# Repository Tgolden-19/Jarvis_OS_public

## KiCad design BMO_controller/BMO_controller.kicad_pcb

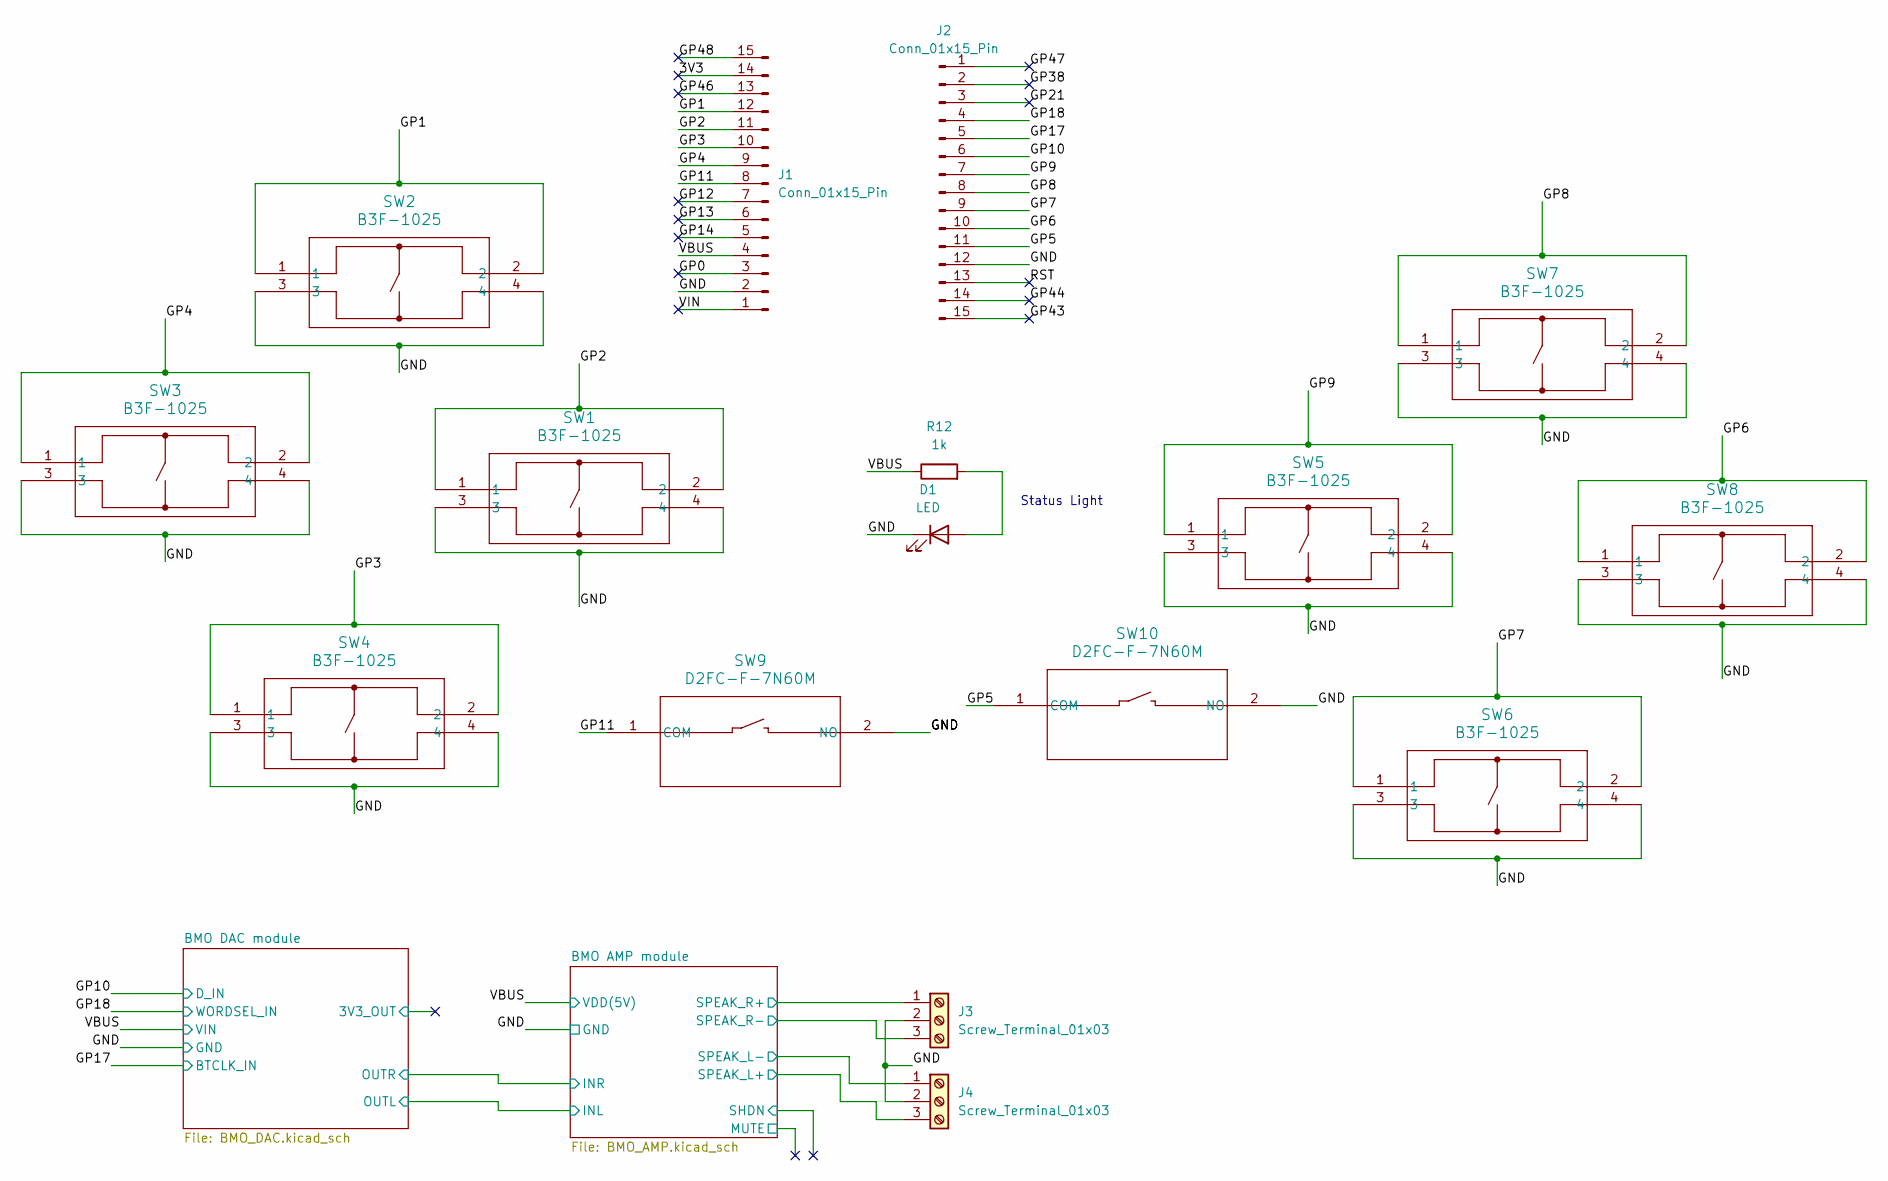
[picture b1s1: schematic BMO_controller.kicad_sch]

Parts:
D1: LED; LED_0201_0603Metric
J1, J2: Conn_01x15_Pin; PinSocket_1x15_P2.54mm_Vertical
J3, J4: Screw_Terminal_01x03; TerminalBlock_4Ucon_1x03_P3.50mm_Horizontal
R12: 1k; R_0201_0603Metric
SW1, SW2, SW3, SW4, SW5, SW6, SW7, SW8: B3F-1025; SW_B3F-1000_OMR
SW9, SW10: D2FC-F-7N60M; SW_D2FC_OMR

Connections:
/3V3: J1.14
/BMO AMP module/SPEAK_L+: J4.3; also elsewhere on the board
/BMO AMP module/SPEAK_L-: J4.1; also elsewhere on the board
/BMO AMP module/SPEAK_R+: J3.1; also elsewhere on the board
/BMO AMP module/SPEAK_R-: J3.3; also elsewhere on the board
/GP0: J1.3
/GP1: J1.12, SW2.1, SW2.2
/GP2: J1.11, SW1.1, SW1.2
/GP3: J1.10, SW4.1, SW4.2
/GP4: J1.9, SW3.1, SW3.2
/GP5: J2.11, SW10.1 (COM)
/GP6: J2.10, SW8.1, SW8.2
/GP7: J2.9, SW6.1, SW6.2
/GP8: J2.8, SW7.1, SW7.2
/GP9: J2.7, SW5.1, SW5.2
/GP10: J2.6; also elsewhere on the board
/GP11: J1.8, SW9.1 (COM)
/GP12: J1.7
/GP13: J1.6
/GP14: J1.5
/GP17: J2.5; also elsewhere on the board
/GP18: J2.4; also elsewhere on the board
/GP21: J2.3
/GP38: J2.2
/GP43: J2.15
/GP44: J2.14
/GP46: J1.13
/GP47: J2.1
/GP48: J1.15
/RST: J2.13
/VBUS: J1.4, R12.1; also elsewhere on the board
/VIN: J1.1
GND: D1.1 (K), J1.2, J2.12, J3.2, J4.2, SW1.3, SW1.4, SW2.3, SW2.4, SW3.3, SW3.4, SW4.3, SW4.4, SW5.3, SW5.4, SW6.3, SW6.4, SW7.3, SW7.4, SW8.3, SW8.4, SW9.2 (NO), SW10.2 (NO); also elsewhere on the board
unnamed: D1.2 (A), R12.2

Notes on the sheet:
Status Light

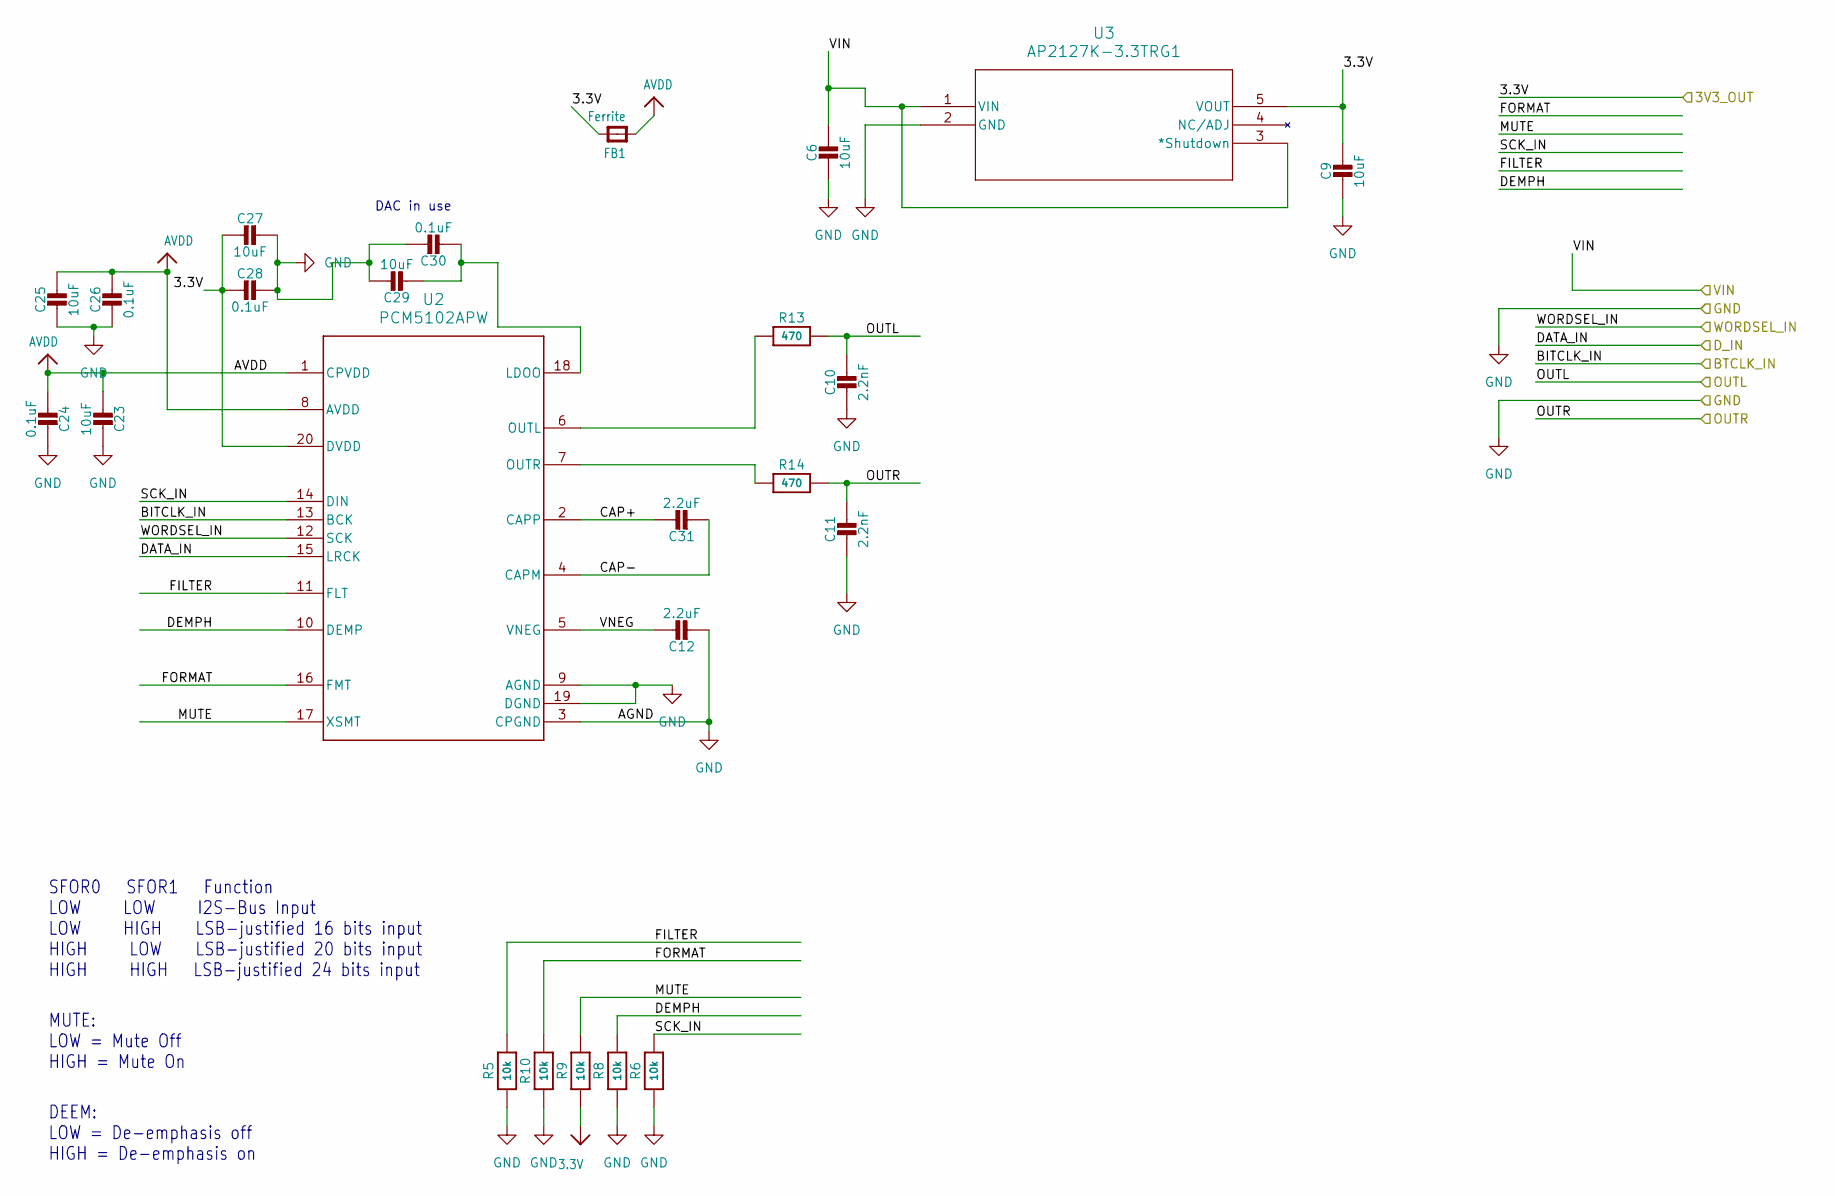
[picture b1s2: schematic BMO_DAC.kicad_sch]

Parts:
C6, C9, C23, C25, C27, C29: 10uF; C_0805_2012Metric
C10, C11: 2.2nF; C_0603_1608Metric
C12, C31: 2.2uF; C_0603_1608Metric
C24, C26, C28, C30: 0.1uF; C_0603_1608Metric
FB1: Ferrite; R_0603_1608Metric_Pad0.98x0.95mm_HandSolder
R5, R6, R8, R9, R10: 10k; R_0603_1608Metric
R13, R14: 470; R_0402_1005Metric
U2: PCM5102APW; PW0020A_M
U3: AP2127K-3.3TRG1; SOT-23-5_AP2127K-3.3TRG1_DIO

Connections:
3.3V: C9.1, C27.1, C28.1, FB1.2, R9.1, U2.20 (DVDD), U3.5 (VOUT)
/BMO DAC module/CAP+: C31.1, U2.2 (CAPP)
/BMO DAC module/CAP-: C31.2, U2.4 (CAPM)
/BMO DAC module/DEMPH: R8.2, U2.10 (DEMP)
/BMO DAC module/FILTER: R5.2, U2.11 (FLT)
/BMO DAC module/FORMAT: R10.2, U2.16 (FMT)
/BMO DAC module/MUTE: R9.2, U2.17 (XSMT)
/BMO DAC module/OUTL: C10.1, R13.2; also elsewhere on the board
/BMO DAC module/OUTR: C11.1, R14.2; also elsewhere on the board
/BMO DAC module/SCK_IN: R6.2, U2.14 (DIN)
/BMO DAC module/VNEG: C12.1, U2.5 (VNEG)
/GP10: U2.15 (LRCK); also elsewhere on the board
/GP17: U2.13 (BCK); also elsewhere on the board
/GP18: U2.12 (SCK); also elsewhere on the board
/VBUS: C6.1, U3.1 (VIN), U3.3 (*Shutdown); also elsewhere on the board
AVDD: C23.1, C24.1, C25.1, C26.1, FB1.1, U2.1 (CPVDD), U2.8 (AVDD)
GND: C6.2, C9.2, C10.2, C11.2, C12.2, C23.2, C24.2, C25.2, C26.2, C27.2, C28.2, C29.2, C30.2, R5.1, R6.1, R8.1, R10.1, U2.3 (CPGND), U2.9 (AGND), U2.19 (DGND), U3.2 (GND); also elsewhere on the board
unnamed: C29.1, C30.1, U2.18 (LDOO)
unnamed: R13.1, U2.6 (OUTL)
unnamed: R14.1, U2.7 (OUTR)

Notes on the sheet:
MUTE: LOW = Mute Off HIGH = Mute On
SFOR0 SFOR1 Function LOW LOW I2S-Bus Input LOW HIGH LSB-justified 16 bits input HIGH LOW LSB-justified 20 bits input HIGH HIGH LSB-justified 24 bits input
DAC in use
DEEM: LOW = De-emphasis off HIGH = De-emphasis on

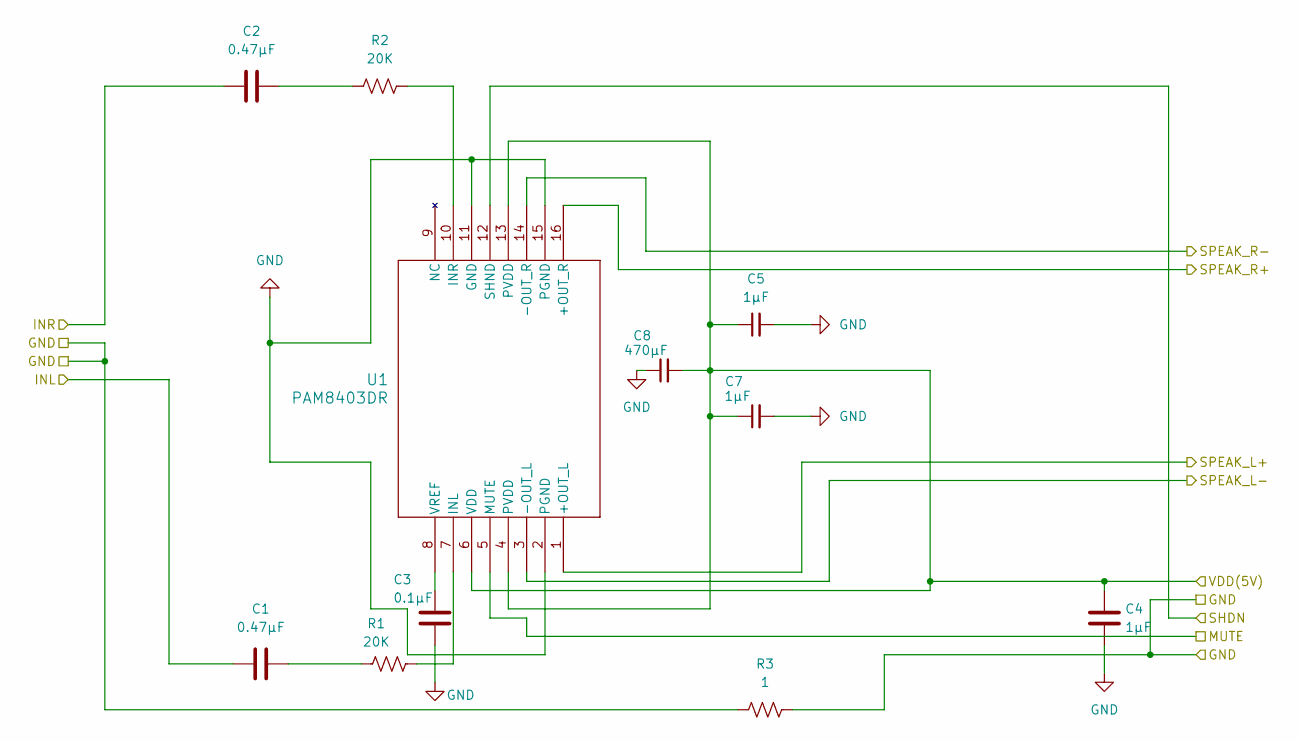
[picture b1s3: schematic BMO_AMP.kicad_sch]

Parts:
C1, C2: 0.47µF; C_0603_1608Metric
C3: 0.1µF; C_0603_1608Metric
C4, C5, C7: 1µF; C_0603_1608Metric
C8: 470µF; C_1812_4532Metric
R1, R2: 20K; R_0603_1608Metric
R3: 1; R_0201_0603Metric
U1: PAM8403DR; SOIC_8403DR_DIO

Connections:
/BMO AMP module/MUTE: U1.5 (MUTE)
/BMO AMP module/SHDN: U1.12 (SHND)
/BMO AMP module/SPEAK_L+: U1.1 (+OUT_L); also elsewhere on the board
/BMO AMP module/SPEAK_L-: U1.3 (-OUT_L); also elsewhere on the board
/BMO AMP module/SPEAK_R+: U1.16 (+OUT_R); also elsewhere on the board
/BMO AMP module/SPEAK_R-: U1.14 (-OUT_R); also elsewhere on the board
/BMO DAC module/OUTL: C1.1; also elsewhere on the board
/BMO DAC module/OUTR: C2.1; also elsewhere on the board
/VBUS: C4.2, C5.1, C7.1, C8.2, U1.4 (PVDD), U1.6 (VDD), U1.13 (PVDD); also elsewhere on the board
GND: C3.1, C4.1, C5.2, C7.2, C8.1, R3.1, R3.2, U1.2 (PGND), U1.11 (GND), U1.15 (PGND); also elsewhere on the board
unnamed: C1.2, R1.1
unnamed: C2.2, R2.1
unnamed: R1.2, U1.7 (INL)
unnamed: R2.2, U1.10 (INR)
unnamed: C3.2, U1.8 (VREF)

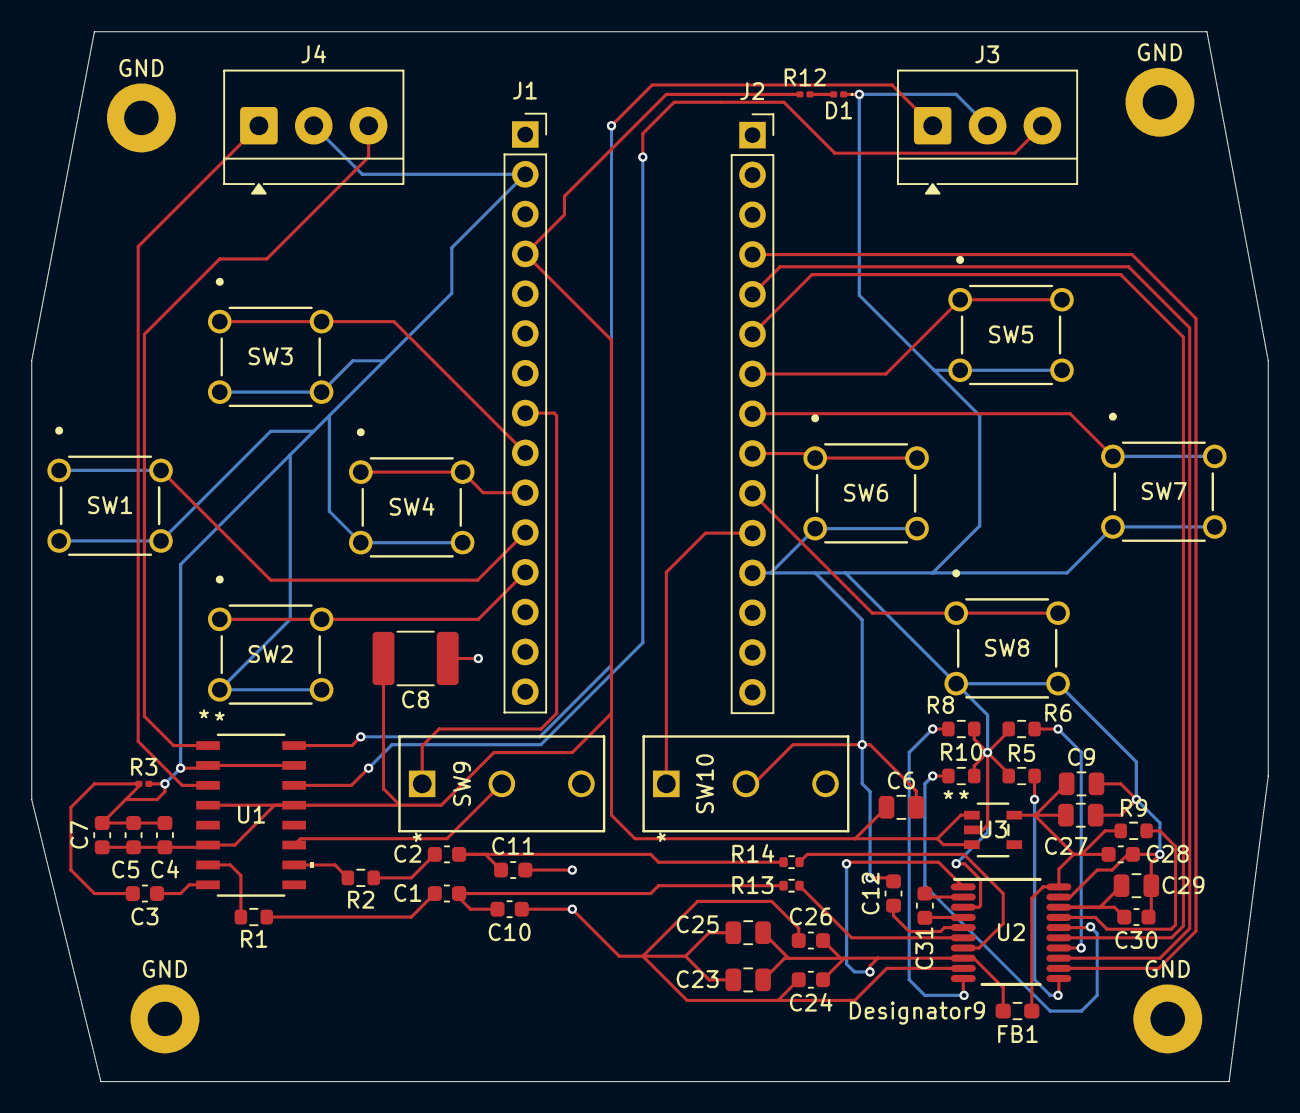
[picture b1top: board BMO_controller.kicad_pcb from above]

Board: 2 copper layers, 78.9 x 67.0 mm, 55 parts (0 on the bottom side), 40 nets.

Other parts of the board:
GND: MountingHole_2.2mm_M2_Pad
GND#2, GND#3, GND#4: MountingHole_2.2mm_M2_Pad

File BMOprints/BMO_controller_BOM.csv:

"Id";"Designator";"Footprint";"Quantity";"Designation";"Supplier and ref";
1;"J2,J1";"PinSocket_1x15_P2.54mm_Vertical";2;"Conn_01x15_Pin";;;
2;"C8";"C_1812_4532Metric";1;"470µF";;;
3;"C27,C23,C25,C9,C6,C29";"C_0805_2012Metric";6;"10uF";;;
4;"C1,C2";"C_0603_1608Metric";2;"0.47µF";;;
5;"SW7,SW4,SW5,SW1,SW8,SW2,SW3,SW6";"SW_B3F-1000_OMR";8;"B3F-1025";;;
6;"C12,C31";"C_0603_1608Metric";2;"2.2uF";;;
7;"C30,C28,C26,C24";"C_0603_1608Metric";4;"0.1uF";;;
8;"R1,R2";"R_0603_1608Metric";2;"20K";;;
9;"C11,C10";"C_0603_1608Metric";2;"2.2nF";;;
10;"U2";"PW0020A_M";1;"PCM5102APW";;;
11;"SW9,SW10";"SW_D2FC_OMR";2;"D2FC-F-7N60M";;;
12;"C5,C4,C7";"C_0603_1608Metric";3;"1µF";;;
13;"J4,J3";"TerminalBlock_4Ucon_1x03_P3.50mm_Horizontal";2;"Screw_Terminal_01x03";;;
14;"R6,R9,R10,R8,R5";"R_0603_1608Metric";5;"10k";;;
15;"C3";"C_0603_1608Metric";1;"0.1µF";;;
16;"FB1";"R_0603_1608Metric_Pad0.98x0.95mm_HandSolder";1;"Ferrite";;;
17;"R13,R14";"R_0402_1005Metric";2;"470";;;
18;"U3";"SOT-23-5_AP2127K-3.3TRG1_DIO";1;"AP2127K-3.3TRG1";;;
19;"R3";"R_0201_0603Metric";1;"1";;;
20;"D1";"LED_0201_0603Metric";1;"LED";;;
21;"R12";"R_0201_0603Metric";1;"1k";;;
22;"U1";"SOIC_8403DR_DIO";1;"PAM8403DR";;;
